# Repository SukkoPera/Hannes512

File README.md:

# Hannes512
Hannes512 is an Open Hardware internal 512 kB RAM Expansion board for the Commodore 16.

## Summary
While making [Hannes256](https://github.com/SukkoPera/Hannes256) two shortcomings became apparent:
* The RAM chips needed to be recovered from old equipment or bought second-hand
* The power draw was probably pretty significant (although I never measured it)

It was pretty obvious that switching to a modern SRAM would alleviate both issues, so I went looking for modern chips I could use and the Alliance AS6C4008 turned out to be a perfect match. Besides, it is 512 kB so I even went beyond the original goals and made all of that available to the C16 (even though that can create incompatibilities, see below).

## Design and Assembly Notes
This board is basically a variant of [Hannes256](https://github.com/SukkoPera/Hannes256#design-and-assembly-notes), so most of what you can read on that page also applies to this board.

One exception is that I reintroduced the ESD protection diodes for the TED that were featured in [Fixteen](https://github.com/SukkoPera/Fixteen). They are U8 and U9 and they are optional.

### RAM Compatibility
Both AS6C4008-55PCN and -55PIN have been tested and work fine. I don't know about any other chips, but it's possible that other SRAMs will work.

AS6C4008 chips can either be bought new from electronic distributors or (probably-) used from AliExpress. I have bought a few of the latter and they were all working correctly.

## Installation
See [Hannes256](https://github.com/SukkoPera/Hannes256#installation).

## Technical Notes
While the mechanism originally devised by Hannes/Solder for 256 kB memory expansion can easily be extended to 512 kB and even 1 MB expansions, it requires that software programmers behave correctly and consider the *default bank* to be bank 15. Unfortunately, some of the software requiring 256 kB that already exists was written with the assumption that no expansion larger than 256 kB would ever surface and sets bits 2/3 of the expansion control register to 0 when wanting to switch to the default bank.

This problem affects [Dream World](img/dreamworld_fd16_startup.png) and even the modern-era [Lykia](img/lykia_fd16_startup.png), for instance. The only real solution is to patch the software, but until someone does that, another option is to just limit memory expansions to 256 kB. After all, there is no software (... yet!) that needs more than that, so it currently looks like an acceptable compromise.

The great news is that this is rather easy to do in Hannes512, you just need to program the GAL with a different file. The [gal directory](gal/) contains a number of different JED files:
* **Hannes512_GAL2x.jed**: These files provide the full 512 kB.
* **Hanns512_G2x256.jed**: These files are limited to 256 kB and are the **recommended ones** to be used at the time being.
* **Hanns512_G2xH37.jed**: These files feature a hack that tries to provide more than 256 kB of memory while making banks 3 and 7 the same bank; it's a temporary hack I made mainly for myself, so please disregard it.

Feel free to open an issue if you have some suggestions on this topic.

## Testing
See [Hannes256](https://github.com/SukkoPera/Hannes256#testing).

## Programming
See [Hannes256](https://github.com/SukkoPera/Hannes256#programming), but keep in mind what is said in the *Technical Notes* above.

## Releases
If you want to get this board produced, you are recommended to get [the latest release](https://github.com/SukkoPera/Hannes512/releases) rather than the current git version, as the latter might be under development and is not guaranteed to be working.

Every release is accompanied by its Bill Of Materials (BOM) file and any relevant notes about it, which you are recommended to read carefully.

## License
The Hannes512 documentation, including the design itself, is copyright &copy; SukkoPera 2022-2023 and is licensed under the [Creative Commons Attribution-NonCommercial-ShareAlike 4.0 International License](https://creativecommons.org/licenses/by-nc-sa/4.0/).

This documentation is distributed *as is* and WITHOUT ANY EXPRESS OR IMPLIED WARRANTIES whatsoever with respect to its functionality, operability or use, including, without limitation, any implied warranties OF MERCHANTABILITY, SATISFACTORY QUALITY, FITNESS FOR A PARTICULAR PURPOSE or infringement. We expressly disclaim any liability whatsoever for any direct, indirect, consequential, incidental or special damages, including, without limitation, lost revenues, lost profits, losses resulting from business interruption or loss of data, regardless of the form of action or legal theory under which the liability may be asserted, even if advised of the possibility or likelihood of such damages.

## Support the Project
If you want to get some boards manufactured, you can get them from PCBWay through this link:

You get my gratitude and cheap, professionally-made and good quality PCBs, I get some credit that will help with this and [other projects](https://www.pcbway.com/project/member/?bmbno=72D33927-5EF6-42). You won't even have to worry about the various PCB options, it's all pre-configured for you!

Also, if you still have to register, [you can use this link](https://www.pcbway.com/setinvite.aspx?inviteid=41100) to get some bonus initial credit (and yield me some more).

You can also buy me a coffee if you want:

## Thanks
* Hannes and Solder for the original design and documentation.
* eslapion for the SRAM enable circuit, saving me endless hours of debugging.
* Levente Hársfalvi (TLC) for plenty of help, in particular with the MOS 6529 replacement circuit.
* siz for the memory test utility.
* Alit Design for the [Crotah font](https://www.fontspace.com/crotah-font-f86873) used for the logo.

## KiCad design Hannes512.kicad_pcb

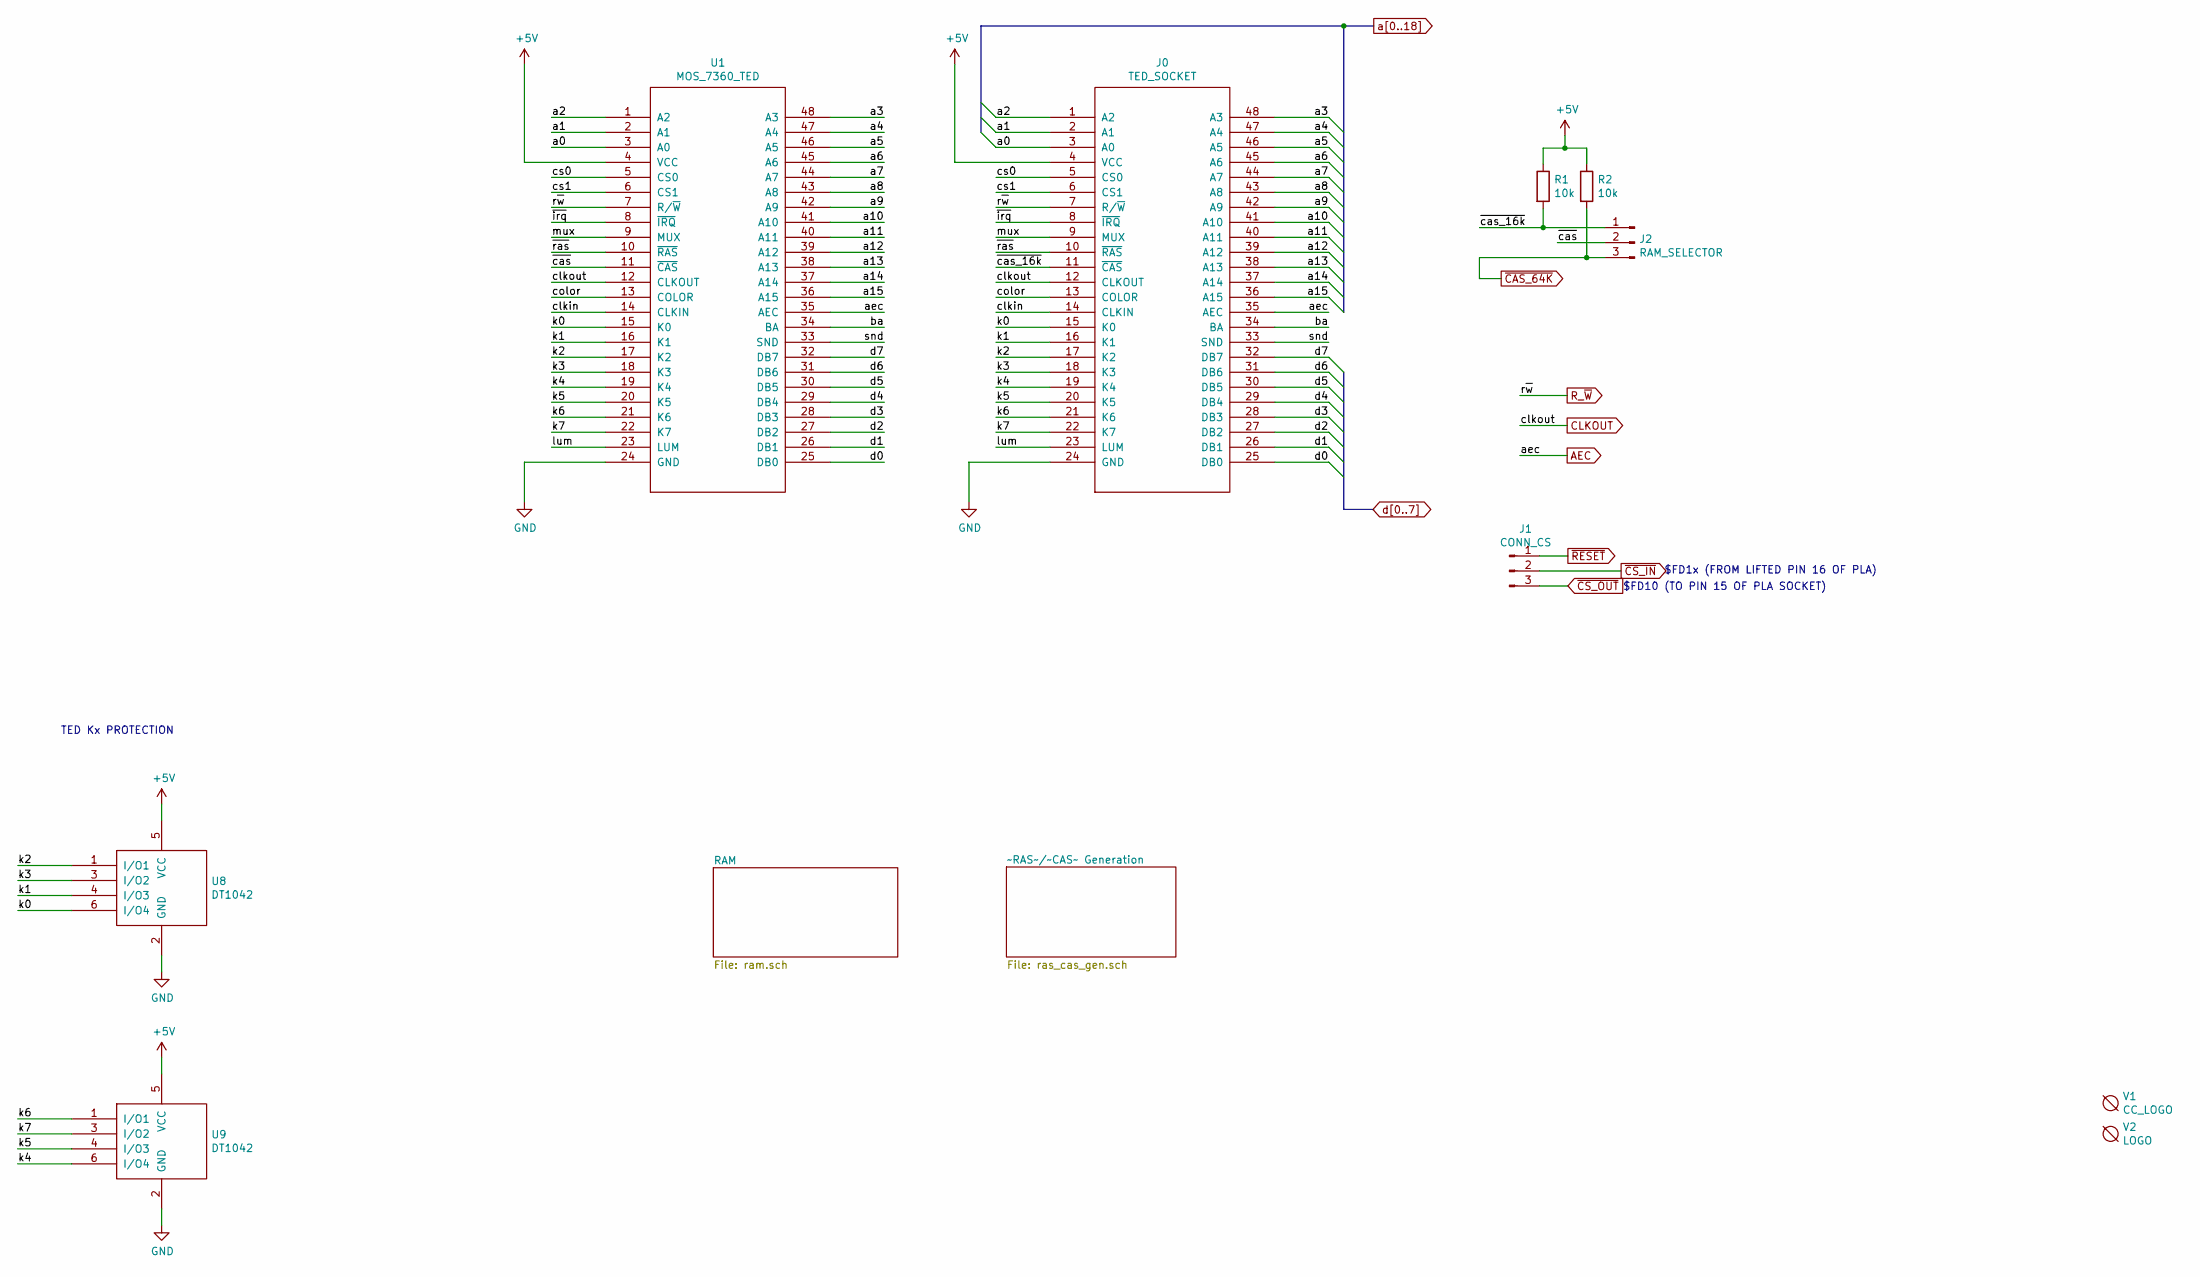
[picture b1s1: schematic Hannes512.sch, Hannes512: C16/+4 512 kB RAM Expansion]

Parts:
J0: TED_SOCKET; DIP-48_W15.24mm_LongPads_ModSilkS
J1: CONN_CS; PinHeader_1x03_P2.54mm_Vertical
J2: RAM_SELECTOR; PinHeader_1x03_P2.54mm_Vertical
R1, R2: 10k; R_0805_2012Metric_Pad1.20x1.40mm_HandSolder
U1: MOS_7360_TED; DIP-48_W15.24mm_Socket_LongPads
U8, U9: DT1042; TSOP-6_1.65x3.05mm_P0.95mm
V1: CC_LOGO; cc_by_nc_sa
V2: LOGO; logo

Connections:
+5V: J0.4 (VCC), R1.1, R2.1, U1.4 (VCC), U8.5 (VCC), U9.5 (VCC); also elsewhere on the board
/ba: J0.34 (BA), U1.34 (BA)
/clkin: J0.14 (CLKIN), U1.14 (CLKIN)
/color: J0.13 (COLOR), U1.13 (COLOR)
/cs0: J0.5 (CS0), U1.5 (CS0)
/cs1: J0.6 (CS1), U1.6 (CS1)
/k0: J0.15 (K0), U1.15 (K0), U8.6 (I/O4)
/k1: J0.16 (K1), U1.16 (K1), U8.4 (I/O3)
/k2: J0.17 (K2), U1.17 (K2), U8.1 (I/O1)
/k3: J0.18 (K3), U1.18 (K3), U8.3 (I/O2)
/k4: J0.19 (K4), U1.19 (K4), U9.6 (I/O4)
/k5: J0.20 (K5), U1.20 (K5), U9.4 (I/O3)
/k6: J0.21 (K6), U1.21 (K6), U9.1 (I/O1)
/k7: J0.22 (K7), U1.22 (K7), U9.3 (I/O2)
/lum: J0.23 (LUM), U1.23 (LUM)
/mux: J0.9 (MUX), U1.9 (MUX)
/snd: J0.33 (SND), U1.33 (SND)
/~cas: J2.2, U1.11 (~CAS)
/~cas_16k: J0.11 (~CAS), J2.1, R1.2
/~irq: J0.8 (~IRQ), U1.8 (~IRQ)
/~ras: J0.10 (~RAS), U1.10 (~RAS)
AEC: J0.35 (AEC), U1.35 (AEC); also elsewhere on the board
CLKOUT: J0.12 (CLKOUT), U1.12 (CLKOUT); also elsewhere on the board
GND: J0.24 (GND), U1.24 (GND), U8.2 (GND), U9.2 (GND); also elsewhere on the board
R_~W: J0.7 (R/~W), U1.7 (R/~W); also elsewhere on the board
a0: J0.3 (A0), U1.3 (A0); also elsewhere on the board
a1: J0.2 (A1), U1.2 (A1); also elsewhere on the board
a2: J0.1 (A2), U1.1 (A2); also elsewhere on the board
a3: J0.48 (A3), U1.48 (A3); also elsewhere on the board
a4: J0.47 (A4), U1.47 (A4); also elsewhere on the board
a5: J0.46 (A5), U1.46 (A5); also elsewhere on the board
a6: J0.45 (A6), U1.45 (A6); also elsewhere on the board
a7: J0.44 (A7), U1.44 (A7); also elsewhere on the board
a8: J0.43 (A8), U1.43 (A8); also elsewhere on the board
a9: J0.42 (A9), U1.42 (A9); also elsewhere on the board
a10: J0.41 (A10), U1.41 (A10); also elsewhere on the board
a11: J0.40 (A11), U1.40 (A11); also elsewhere on the board
a12: J0.39 (A12), U1.39 (A12); also elsewhere on the board
a13: J0.38 (A13), U1.38 (A13); also elsewhere on the board
a14: J0.37 (A14), U1.37 (A14); also elsewhere on the board
a15: J0.36 (A15), U1.36 (A15); also elsewhere on the board
d0: J0.25 (DB0), U1.25 (DB0); also elsewhere on the board
d1: J0.26 (DB1), U1.26 (DB1); also elsewhere on the board
d2: J0.27 (DB2), U1.27 (DB2); also elsewhere on the board
d3: J0.28 (DB3), U1.28 (DB3); also elsewhere on the board
d4: J0.29 (DB4), U1.29 (DB4); also elsewhere on the board
d5: J0.30 (DB5), U1.30 (DB5); also elsewhere on the board
d6: J0.31 (DB6), U1.31 (DB6); also elsewhere on the board
d7: J0.32 (DB7), U1.32 (DB7); also elsewhere on the board
~CAS_64K: J2.3, R2.2; also elsewhere on the board
~CS_IN: J1.2; also elsewhere on the board
~CS_OUT: J1.3; also elsewhere on the board
~RESET: J1.1; also elsewhere on the board

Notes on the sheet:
$FD1x (FROM LIFTED PIN 16 OF PLA)
$FD10 (TO PIN 15 OF PLA SOCKET)
TED Kx PROTECTION

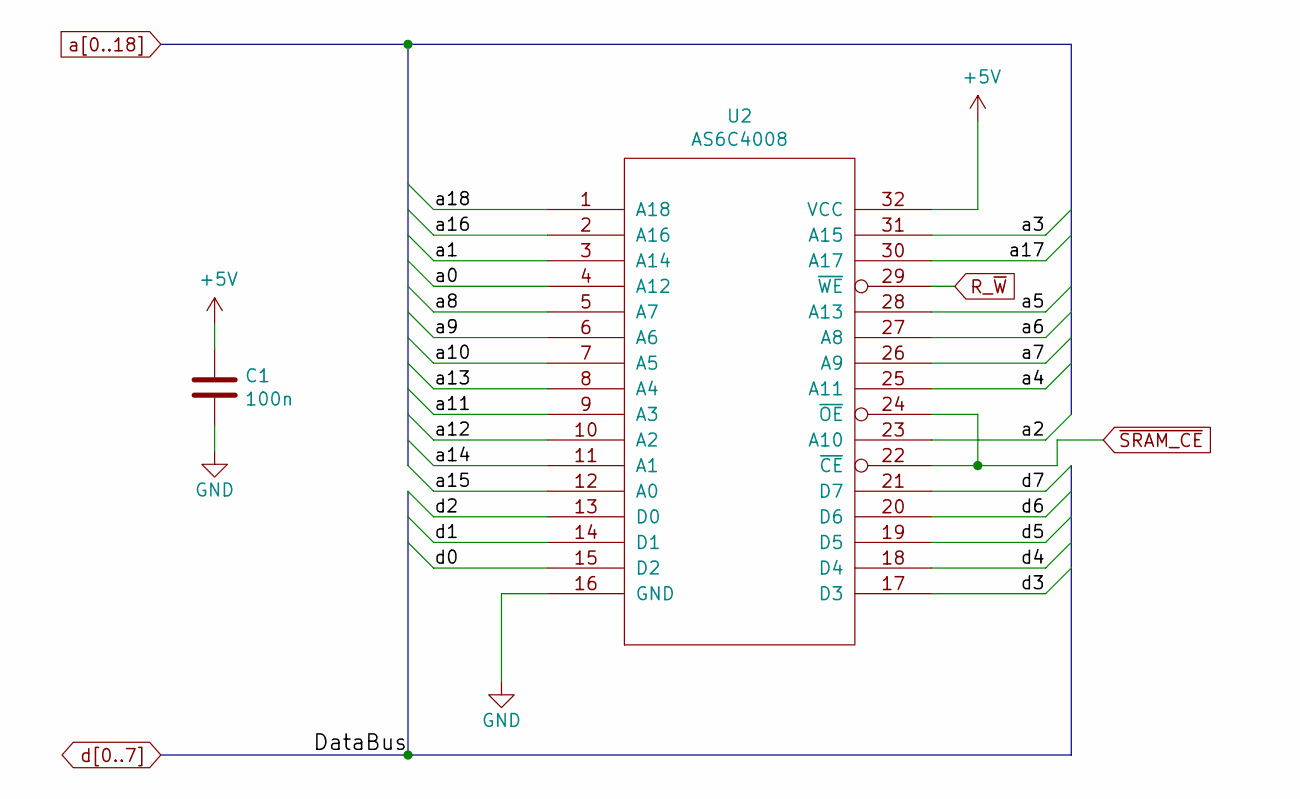
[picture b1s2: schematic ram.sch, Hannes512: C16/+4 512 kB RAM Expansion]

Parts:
C1: 100n; C_0805_2012Metric_Pad1.18x1.45mm_HandSolder
U2: AS6C4008; DIP-32_W15.24mm_Socket_LongPads

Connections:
+5V: C1.1, U2.32 (VCC); also elsewhere on the board
GND: C1.2, U2.16 (GND); also elsewhere on the board
R_~W: U2.29 (~WE); also elsewhere on the board
a0: U2.4 (A12); also elsewhere on the board
a1: U2.3 (A14); also elsewhere on the board
a2: U2.23 (A10); also elsewhere on the board
a3: U2.31 (A15); also elsewhere on the board
a4: U2.25 (A11); also elsewhere on the board
a5: U2.28 (A13); also elsewhere on the board
a6: U2.27 (A8); also elsewhere on the board
a7: U2.26 (A9); also elsewhere on the board
a8: U2.5 (A7); also elsewhere on the board
a9: U2.6 (A6); also elsewhere on the board
a10: U2.7 (A5); also elsewhere on the board
a11: U2.9 (A3); also elsewhere on the board
a12: U2.10 (A2); also elsewhere on the board
a13: U2.8 (A4); also elsewhere on the board
a14: U2.11 (A1); also elsewhere on the board
a15: U2.12 (A0); also elsewhere on the board
a16: U2.2 (A16); also elsewhere on the board
a17: U2.30 (A17); also elsewhere on the board
a18: U2.1 (A18); also elsewhere on the board
d0: U2.15 (D2); also elsewhere on the board
d1: U2.14 (D1); also elsewhere on the board
d2: U2.13 (D0); also elsewhere on the board
d3: U2.17 (D3); also elsewhere on the board
d4: U2.18 (D4); also elsewhere on the board
d5: U2.19 (D5); also elsewhere on the board
d6: U2.20 (D6); also elsewhere on the board
d7: U2.21 (D7); also elsewhere on the board
~SRAM_CE: U2.22 (~CE), U2.24 (~OE); also elsewhere on the board

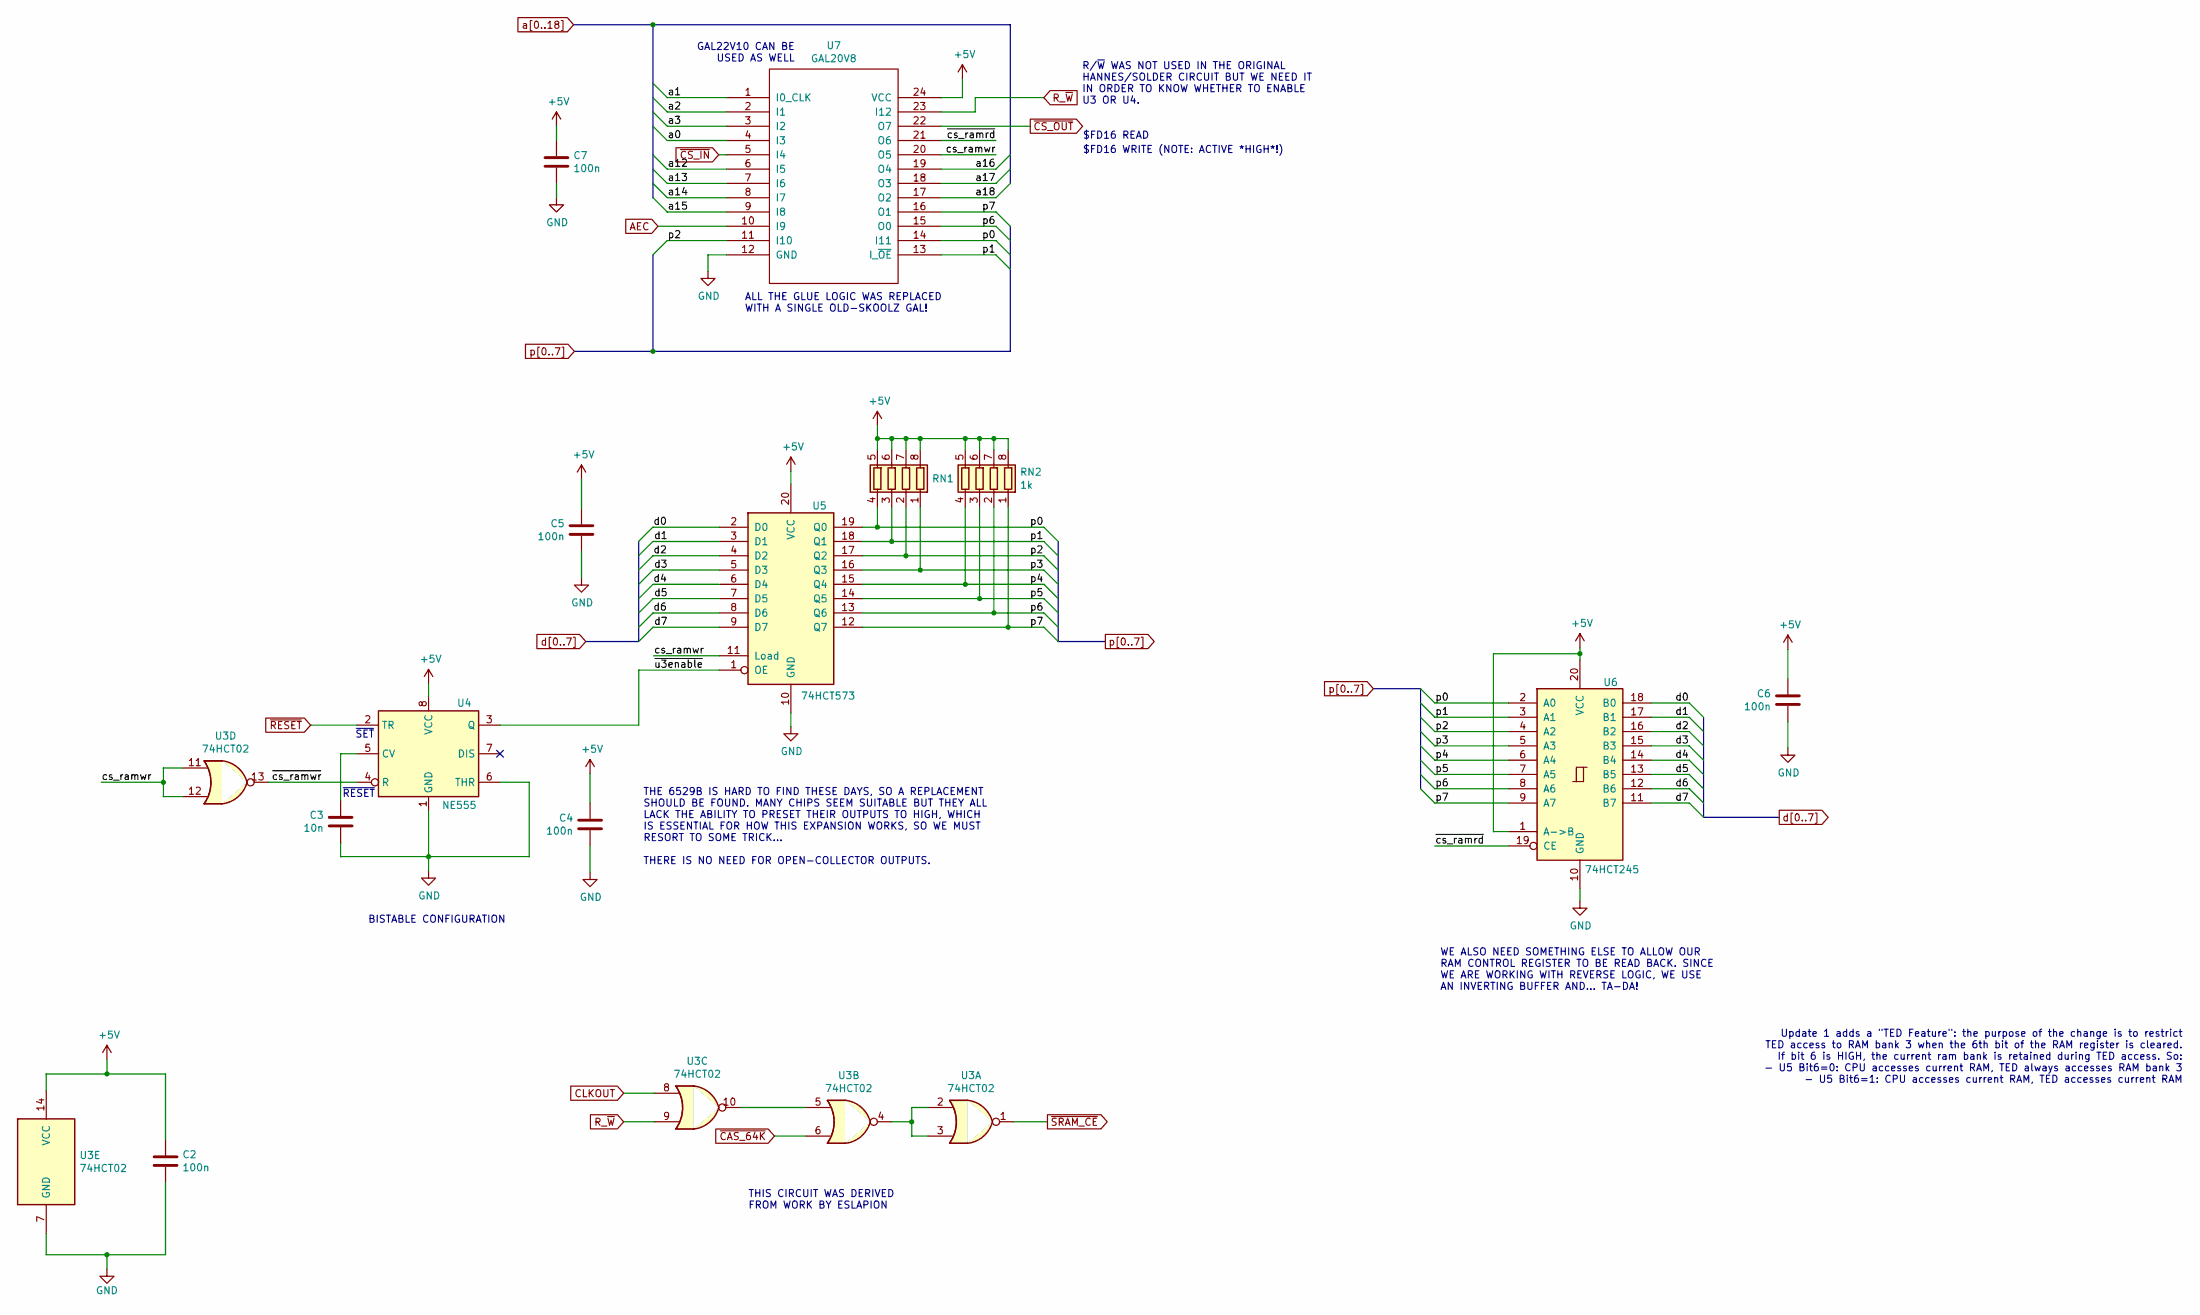
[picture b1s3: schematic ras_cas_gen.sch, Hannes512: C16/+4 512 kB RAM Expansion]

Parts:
C2, C4, C5, C6, C7: 100n; C_0805_2012Metric_Pad1.18x1.45mm_HandSolder
C3: 10n; C_0805_2012Metric_Pad1.18x1.45mm_HandSolder
RN1, RN2: 1k; R_Array_Convex_4x0603
U3: 74HCT02; SOIC-14_3.9x8.7mm_P1.27mm
U4: NE555; SOIC-8_3.9x4.9mm_P1.27mm
U5: 74HCT573; SO-20_5.3x12.6mm_P1.27mm; MouserPN 595-SN74HCT573NSR
U6: 74HCT245; SO-20_5.3x12.6mm_P1.27mm; MouserPN 595-SN74HCT245ANSR
U7: GAL20V8; DIP-24_W7.62mm_Socket

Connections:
+5V: C2.1, C4.1, C5.1, C6.1, C7.1, RN1.5 (R4.2), RN1.6 (R3.2), RN1.7 (R2.2), RN1.8 (R1.2), RN2.5 (R4.2), RN2.6 (R3.2), RN2.7 (R2.2), RN2.8 (R1.2), U3.14 (VCC), U4.8 (VCC), U5.20 (VCC), U6.1 (A->B), U6.20 (VCC), U7.24 (VCC); also elsewhere on the board
/~RAS~/~CAS~ Generation/cs_ramwr: U3.11, U3.12, U5.11 (Load), U7.20 (O5)
/~RAS~/~CAS~ Generation/~cs_ramrd: U6.19 (CE), U7.21 (O6)
/~RAS~/~CAS~ Generation/~cs_ramwr: U3.13, U4.4 (R)
/~RAS~/~CAS~ Generation/~u3enable: U4.3 (Q), U5.1 (OE)
AEC: U7.10 (I9); also elsewhere on the board
CLKOUT: U3.8; also elsewhere on the board
GND: C2.2, C3.2, C4.2, C5.2, C6.2, C7.2, U3.7 (GND), U4.1 (GND), U4.6 (THR), U5.10 (GND), U6.10 (GND), U7.12 (GND); also elsewhere on the board
unnamed: C3.1, U4.5 (CV)
unnamed: U3.2, U3.3, U3.4
unnamed: U3.5, U3.10
R_~W: U3.9, U7.23 (I12); also elsewhere on the board
a0: U7.4 (I3); also elsewhere on the board
a1: U7.1 (I0_CLK); also elsewhere on the board
a2: U7.2 (I1); also elsewhere on the board
a3: U7.3 (I2); also elsewhere on the board
a12: U7.6 (I5); also elsewhere on the board
a13: U7.7 (I6); also elsewhere on the board
a14: U7.8 (I7); also elsewhere on the board
a15: U7.9 (I8); also elsewhere on the board
a16: U7.19 (O4); also elsewhere on the board
a17: U7.18 (O3); also elsewhere on the board
a18: U7.17 (O2); also elsewhere on the board
d0: U5.2 (D0), U6.18 (B0); also elsewhere on the board
d1: U5.3 (D1), U6.17 (B1); also elsewhere on the board
d2: U5.4 (D2), U6.16 (B2); also elsewhere on the board
d3: U5.5 (D3), U6.15 (B3); also elsewhere on the board
d4: U5.6 (D4), U6.14 (B4); also elsewhere on the board
d5: U5.7 (D5), U6.13 (B5); also elsewhere on the board
d6: U5.8 (D6), U6.12 (B6); also elsewhere on the board
d7: U5.9 (D7), U6.11 (B7); also elsewhere on the board
p0: RN1.4 (R4.1), U5.19 (Q0), U6.2 (A0), U7.14 (I11)
p1: RN1.3 (R3.1), U5.18 (Q1), U6.3 (A1), U7.13 (I_~OE)
p2: RN1.2 (R2.1), U5.17 (Q2), U6.4 (A2), U7.11 (I10)
p3: RN1.1 (R1.1), U5.16 (Q3), U6.5 (A3)
p4: RN2.4 (R4.1), U5.15 (Q4), U6.6 (A4)
p5: RN2.3 (R3.1), U5.14 (Q5), U6.7 (A5)
p6: RN2.2 (R2.1), U5.13 (Q6), U6.8 (A6), U7.15 (O0)
p7: RN2.1 (R1.1), U5.12 (Q7), U6.9 (A7), U7.16 (O1)
~CAS_64K: U3.6; also elsewhere on the board
~CS_IN: U7.5 (I4); also elsewhere on the board
~CS_OUT: U7.22 (O7); also elsewhere on the board
~RESET: U4.2 (TR); also elsewhere on the board
~SRAM_CE: U3.1; also elsewhere on the board

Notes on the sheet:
Update 1 adds a "TED Feature": the purpose of the change is to restrict TED access to RAM bank 3 when the 6th bit of the RAM register is cleared. If bit 6 is HIGH, the current ram bank is retained during TED access. So: - U5 Bit6=0: CPU accesses current RAM, TED always accesses RAM bank 3 - U5 Bit6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
THE 6529B IS HARD TO FIND THESE DAYS, SO A REPLACEMENT SHOULD BE FOUND. MANY CHIPS SEEM SUITABLE BUT THEY ALL LACK THE ABILITY TO PRESET THEIR OUTPUTS TO HIGH, WHICH IS ESSENTIAL FOR HOW THIS EXPANSION WORKS, SO WE MUST RESORT TO SOME TRICK... THERE IS NO NEED FOR OPEN-COLLECTOR OUTPUTS.
ALL THE GLUE LOGIC WAS REPLACED WITH A SINGLE OLD-SKOOLZ GAL!
WE ALSO NEED SOMETHING ELSE TO ALLOW OUR RAM CONTROL REGISTER TO BE READ BACK. SINCE WE ARE WORKING WITH REVERSE LOGIC, WE USE AN INVERTING BUFFER AND... TA-DA!
GAL22V10 CAN BE USED AS WELL
$FD16 READ
~SET
~RESET
BISTABLE CONFIGURATION
R/~W~ WAS NOT USED IN THE ORIGINAL HANNES/SOLDER CIRCUIT BUT WE NEED IT IN ORDER TO KNOW WHETHER TO ENABLE U3 OR U4.
THIS CIRCUIT WAS DERIVED FROM WORK BY ESLAPION
$FD16 WRITE (NOTE: ACTIVE *HIGH*!)

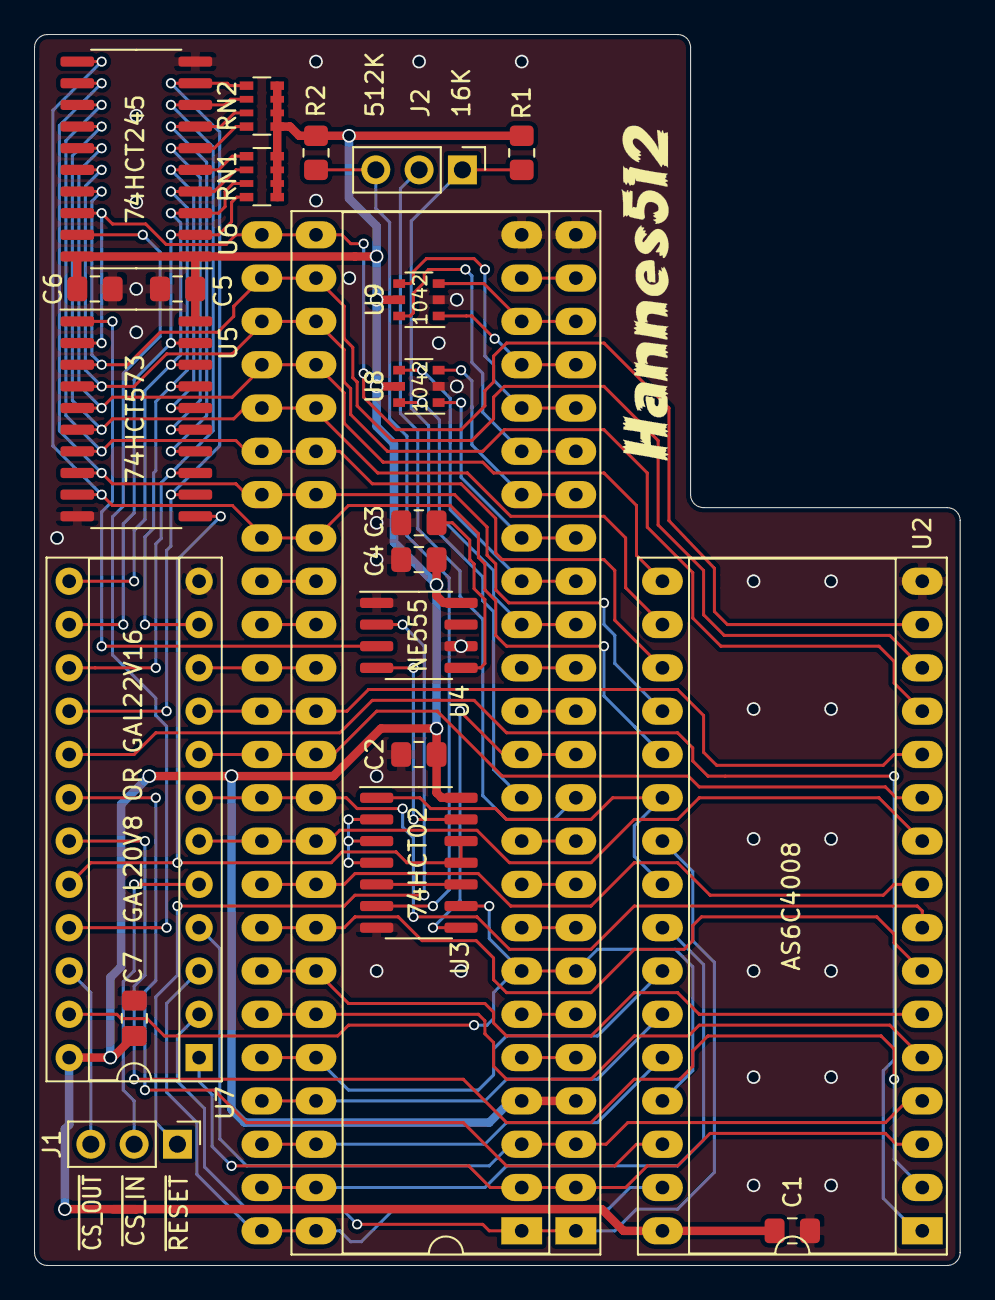
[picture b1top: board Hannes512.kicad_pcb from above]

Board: 2 copper layers, 54.3 x 72.2 mm, 25 parts (1 on the bottom side), 72 nets.

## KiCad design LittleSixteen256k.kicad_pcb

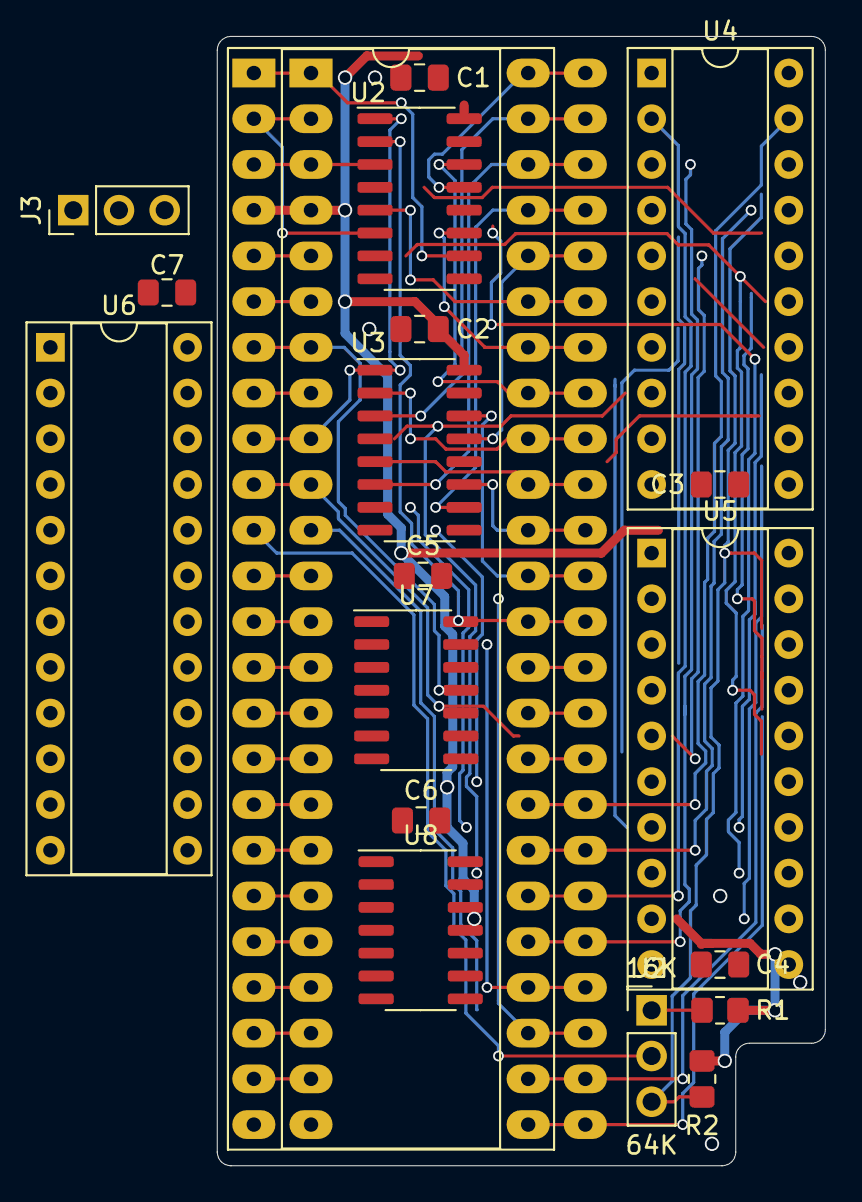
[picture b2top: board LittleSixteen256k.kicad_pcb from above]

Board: 2 copper layers, 33.8 x 62.7 mm, 20 parts (0 on the bottom side), 68 nets.

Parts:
C1, C2, C3, C4, C5, C6, C7: 100n; C_0805_2012Metric_Pad1.18x1.45mm_HandSolder
J1: TED_SOCKET; DIP-48_W15.24mm_LongPads_ModSilkS
J2: RAM_SELECTOR; PinHeader_1x03_P2.54mm_Vertical
J3: CONN_CS; PinHeader_1x03_P2.54mm_Vertical
R1, R2: 10k; R_0805_2012Metric_Pad1.20x1.40mm_HandSolder
U1: MOS_7360_TED; DIP-48_W15.24mm_Socket_LongPads
U2, U3: 74LS257; SOIC-16_3.9x9.9mm_P1.27mm
U4, U5: XX4256; DIP-20_W7.62mm_Socket
U6: GAL20V8; DIP-24_W7.62mm_Socket
U7, U8: 74HCT74; SOIC-14_3.9x8.7mm_P1.27mm

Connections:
+5V: C1.1, C3.1, C4.1, C5.1, C6.1, U4.10, U5.10, U6.24, U7.1, U7.13, U7.14, U8.1, U8.13, U8.14
/ba: J1.34, U1.34
/clkin: J1.14, U1.14
/clkout: J1.12, U1.12
/color: J1.13, U1.13
/cs0: J1.5, U1.5
/cs1: J1.6, U1.6
/k0: J1.15, U1.15
/k1: J1.16, U1.16
/k2: J1.17, U1.17
/k3: J1.18, U1.18
/k4: J1.19, U1.19
/k5: J1.20, U1.20
/k6: J1.21, U1.21
/k7: J1.22, U1.22
/lum: J1.23, U1.23
/snd: J1.33, U1.33
/~RAS~/~CAS~ Generation/~cs_ram: U6.22, U7.3, U7.11, U8.3, U8.11
/~cas: J2.2, U1.11
/~cas_16k: J1.11, J2.1, R1.2
/~irq: J1.8, U1.8
AEC: J1.35, U1.35, U6.16
GND: C1.2, C2.2, C3.2, C4.2, C5.2, C6.2, C7.2, J1.24, U1.24, U2.8, U2.15, U3.8, U3.15, U4.16, U4.20, U5.16, U5.20, U6.12, U7.7, U8.7
MUX: J1.9, U1.9, U2.1, U3.1, U6.10
unnamed: U6.11, U7.5
unnamed: U6.13, U7.9
unnamed: U6.14, U8.5
unnamed: U6.15, U8.9
R_~W: J1.7, U1.7, U4.3, U5.3
VCC: C2.1, C7.1, J1.4, R1.1, R2.1, U1.4, U2.16, U3.16
a0: J1.3, U1.3, U2.3, U6.1, U6.6
a1: J1.2, U1.2, U2.6, U6.2, U6.7
a2: J1.1, U1.1, U2.10, U6.3, U6.8
a3: J1.48, U1.48, U2.13, U6.4, U6.9
a4: J1.47, U1.47, U3.3
a5: J1.46, U1.46, U3.6
a6: J1.45, U1.45, U3.10
a7: J1.44, U1.44, U3.13
a8: J1.43, U1.43, U2.5
a9: J1.42, U1.42, U2.11
a10: J1.41, U1.41, U2.14
a11: J1.40, U1.40, U3.2
a12: J1.39, U1.39, U3.5
a13: J1.38, U1.38, U3.11
a14: J1.37, U1.37, U3.14
a15: J1.36, U1.36, U2.2
d0: J1.25, U1.25, U5.1, U7.2
d1: J1.26, U1.26, U5.2, U7.12
d2: J1.27, U1.27, U5.18
d3: J1.28, U1.28, U5.19
d4: J1.29, U1.29, U4.1
d5: J1.30, U1.30, U4.2
d6: J1.31, U1.31, U4.18, U8.2
d7: J1.32, U1.32, U4.19, U8.12
m0: U2.4, U4.6, U5.6
m1: U2.7, U4.7, U5.7
m2: U2.9, U4.8, U5.8
m3: U2.12, U4.9, U5.9
m4: U3.4, U4.11, U5.11
m5: U3.7, U4.12, U5.12
m6: U3.9, U4.13, U5.13
m7: U3.12, U4.14, U5.14
m8: U4.15, U5.15, U6.20
~CAS_64K: J2.3, R2.2, U4.17, U5.17
~CS_IN: J3.2, U6.5
~CS_OUT: J3.3, U6.21
~RAS: J1.10, U1.10, U4.4, U5.4
~RESET: J3.1, U7.4, U7.10, U8.4, U8.10

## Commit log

2022-07-26 Initial dsegin, should match Hannes's
2022-07-26 Add decoupling caps
2022-07-26 Apply "Update 1" introducing the "TED Feature" Restricts TED access to RAM bank 3 when the 6th bit of the RAM register is cleared.
2022-07-29 Hopefully we now have the schematics for a fully working internal RAM expansion
2022-07-29 Switch out the MOS 6529
2022-07-29 Switch all glue logic to a GAL
2022-07-30 Start working on PCB
2022-08-16 Fix address pins
2022-09-19 LittleSixteen256k -> Hannes256
2022-09-19 Routing in progress
2022-09-25 Switch to 41256 RAM This will handle the refresh properly despite needing 8 chips instead of 2, sigh...
2022-09-25 Routing almost done
2022-09-26 Initial routing complete
2022-09-26 Yeah yeah yeah
2022-09-26 Add credits
2022-09-26 Add logo and ready for V1rc1
2022-10-08 Cosmetic fixes
2022-10-24 Add GAL22 files
2022-10-25 Bring R/W to the GAL We'll have to write an essay on this...
2022-10-25 Center C13 within U13 The socket won't fit otherwise!
2022-10-25 Cosmetics
2022-10-26 Only enable RAM register during writes
2022-10-29 Add a 74x245 to provide RAM register read functionality
2022-12-08 Use a different MOS 6529 replacement circuit, courtesy of TLC
2022-12-11 Update silkscreen
2023-01-09 Fix U3 Latch Enable, sigh... GAL equations TBD
2023-01-09 Update GAL equations for Latch Enable modifications
2023-02-15 Use bank 3 when in non-switchable range *Maybe* this only reshuffles the banks around, but anyway it results in simplified equations that let us avoid using an intermediate signal, freeing one pin - 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
2023-02-22 More routing
2023-02-26 ROuting done
2023-02-27 Update GAL equations
2023-02-27 Relabel all components
2023-02-27 Hannes256 -> Hannes512
2023-02-27 Ready for V1
2023-02-27 Some rerouting
2023-02-27 More rerouting
2023-02-28 Relocate RN1/2 on top
2023-03-14 Add TED Kx Protection
2023-03-14 Ground plane improvements
2023-03-14 Add missing file
2023-12-29 Add part numbers
2023-12-29 Direct unbanked accesses to slot 3 rather than 7
2023-12-31 Add more GAL files
2023-12-31 Add renders
2023-12-31 Update board link

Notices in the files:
Hannes512.kicad_pcb:
Licensed under CC BY-NC-SA 4.0
© SukkoPera 2023
LittleSixteen256k.kicad_pcb:
Licensed under CERN OHL v.1.2
